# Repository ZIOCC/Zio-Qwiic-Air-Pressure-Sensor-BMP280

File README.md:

# Zio Qwiic Air Pressure Sensor BMP280

> This product can be available for purchase [here](https://www.smart-prototyping.com/Zio-Qwiic-Air-Pressure-Sensor-BMP280).

##### Description

This little board features a high precision BMP280 Barometric Pressure and Altitude Sensor by Bosch. The sensor is not only capable of sensing pressure and altitude but it also environmental temperature, almost all the data you need around atmospheric conditions.

The sensor is one of the best low-cost solutions when it comes to take precise environmental data. The barometric pressure has a ±1.0 hPa absolute accuracy, on pressures from 200 hPa to 11hPa. Temperature measurements are pretty accurate also, with a ±1.0°C accuracy on temperatures between -40 and 85°C.

As the altitude increases, the atmospheric pressure decreases - and due to the sensor high accuracy on taking pressure measurements - the altitude can also be calculated. With a  ±1 meter precision on altitude sensing. 

Great sensor right? As a member of our Qwiic family, the board incorporates the Qwiic connector for easy wiring to use I2C interface. But this great little sensor can use either I2C or SPI so we made it pretty accessible to switch to SPI. Simply solder the header pins provided if you want to go for it!

##### Specification

* Operation Voltage: 3.3V
* Current Consumption: 2.7μA
* Barometric Pressure Measure
  * Range: 300 – 1100 hPa
  * Accuracy: ±1.0 hPa
* Temperature Measurement
  * Range: -40 to 85
  * Accuracy: ±1
* Interface: I2C and SPI
* Port: I2C (selectable address at 0x77(default) and 0x76)
* Dimensions: 16.5mm x 25.3mm
* Weight: 1.4g

##### Links

* [Eagle File & Schematic](https://github.com/ZIOCC/Zio-Qwiic-Air-Pressure-Sensor-BMP280)
* [BMP280 library Link](https://github.com/adafruit/Adafruit_BMP280_Library)
* [BMP280 Datasheet](https://cdn-shop.adafruit.com/datasheets/BST-BMP280-DS001-11.pdf)

> ###### About Zio
> Zio is a new line of open sourced, compact, and grid layout boards, fully integrated for Arduino and Qwiic ecosystem. Designed ideally for wearables, robotics, small-space limitations or other on the go projects. Check out other awesome Zio products [here](https://www.smart-prototyping.com/Zio).

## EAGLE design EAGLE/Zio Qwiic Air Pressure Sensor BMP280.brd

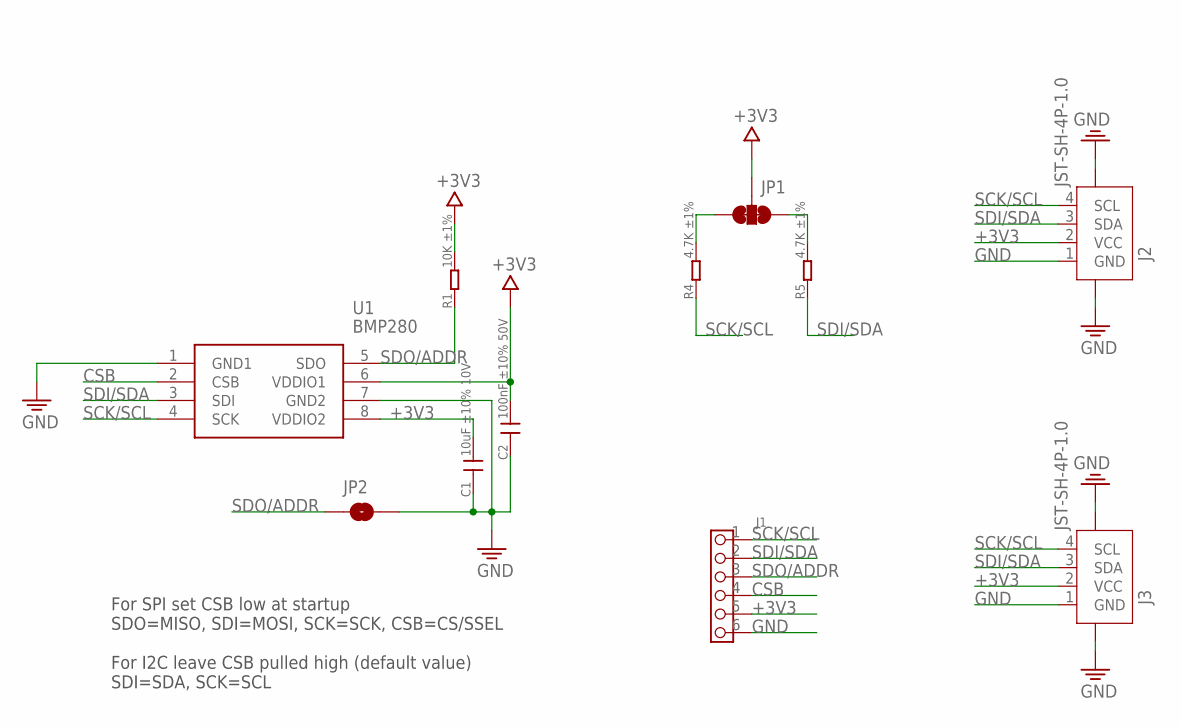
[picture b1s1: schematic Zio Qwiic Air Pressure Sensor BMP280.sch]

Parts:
C1: 10uF ±10% 10V; C0603
C2: 100nF ±10% 50V; C0603
J1: HEADER-6P-60/35MIL; 6P-2.54-60/35MIL
J2, J3: JST-SH-4P-1.0; JST-SH-4P
JP1: SMT-JUMPER_3_2-NC_TRACE
JP2: JUMPER-SMT_2_NC_PASTE_NOCREM; SMT-JUMPER_2_NC_PASTE_SILK_NOCREM
R1: 10K ±1%; R0603
R4, R5: 4.7K ±1%; R0603
U1: BMP280; 8-PIN-METAL-LID-LGA

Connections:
+3V3: C1.2, C2.2, J1.5, J2.2 (VCC), J3.2 (VCC), JP1.2, R1.2, U1.6 (VDDIO1), U1.8 (VDDIO2)
CSB: J1.4, U1.2 (CSB)
GND: C1.1, C2.1, J1.6, J2.1 (GND), J2.NC1 (5), J2.NC2 (6), J3.1 (GND), J3.NC1 (5), J3.NC2 (6), JP2.2, U1.1 (GND1), U1.7 (GND2)
unnamed: JP1.3, R4.2
unnamed: JP1.1, R5.2
SCK/SCL: J1.1, J2.4 (SCL), J3.4 (SCL), R4.1, U1.4 (SCK)
SDI/SDA: J1.2, J2.3 (SDA), J3.3 (SDA), R5.1, U1.3 (SDI)
SDO/ADDR: J1.3, JP2.1, R1.1, U1.5 (SDO)

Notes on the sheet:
For SPI set CSB low at startup SDO=MISO, SDI=MOSI, SCK=SCK, CSB=CS/SSEL For I2C leave CSB pulled high (default value) SDI=SDA, SCK=SCL

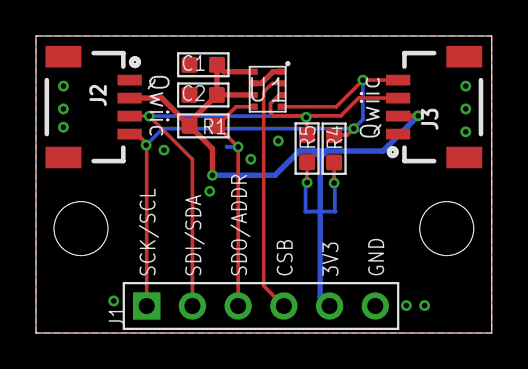
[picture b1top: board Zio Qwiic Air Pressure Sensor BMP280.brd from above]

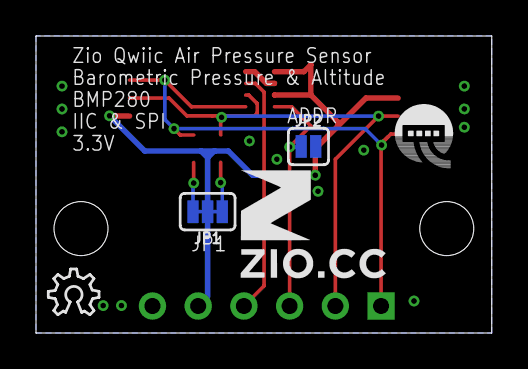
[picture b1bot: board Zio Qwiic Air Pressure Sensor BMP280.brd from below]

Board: 2 copper layers, 25.3 x 16.5 mm, 14 parts (5 on the bottom side), 8 nets.

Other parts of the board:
U$4: 6MM
U$5: QWIIC-LOGO-BASIC
U$6: OSHW_6X100_NOTEXT
